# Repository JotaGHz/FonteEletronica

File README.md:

# Projeto Fonte de Tensão 12V, Eletrônica para Computação, BCC 020. ICMC USP São Carlos
## Grupo:
  ## Joao Francisco Caprioli Barbosa Camargo de Pinho
  ## 10748500
## O Projeto
Nesse projeto, o grupo deve desenvolver uma fonte de Tensão Variável de 3V a 12V, com capacidade de 100mA. Também, deve anexar ao projeto no GitHub o circuito no site de simulação Falstad, uma imagem do circuito no site, e uma simulação do projeto no EAGLE, junto com a simulação da placa do circuito.

  # Simulacão do Falstad
  
  http://tinyurl.com/ydexx9xs
  
  ## Imagem da Simulação
  
  # Componentes usados e preços
    
    Capacitor 470 uF  25V            R$  0,33
    Transformador 110/220V -> 12+12V R$ 16,45
    Resistor 1k *3                   R$  0,24
    Resistor 120 Ohms                R$  0,23
    Resistor 5k1                     R$  0,08
    Potenciômetro 10k   MAX=0,2W     R$  1,46
    LED Vermelho                     R$  0,24
    Diodo Zener 13V     MAX=0,5W     R$  0,14
    Ponte Retificadora   25A         R$  4,94
    Transistor NPN BC337             R$  0,17
    -----------------------------------------
    Total                            R$ 24,28
  # Explicação das peças escolhidas

## Transformador 127V para 24V
  O transformador é necessário para diminuir a voltagem que passa pelo circuito. Um transformador 5:1, ou transforma 127V em cerca de 24V, facilitou a escolha das outras peças, e deu uma margem de erro grande para o resto do circuito.

## Ponte Retificadora
  A ponte retificadora serve pra "converter" a corrente alternada em corrente contínua, gerando um polo positivo em cima e um negativo em baixo, olhando para o circuito no Falstad.

## Capacitor 470uF
  O capacitor "estabiliza" a tensão de 24V. O capacitor serve para manter a corrente estável quando ela alternar. Esse capacitor tem tensão máxima suportada de 35V, sendo perfeito para o circuito. Sem o capacitor, a tensão varia muito, e poderia queimar aparelhos conectados à fonte.

## LED Vermelho e Resistor 2k
  O LED Vermelho se conecta em paralelo com o capacitor. Sem nenhum resistor, o LED "quebraria" o circuito e causaria um curto-circuito, conectando os polos positivo e negativo. O uso de 2k Ohms é para diminuir a corrente gasta pelo LED, e ser um resistor fácil de construir em série com 2 resistores 1k.
  
## Diodo Zener
  O Diodo Zener serve para "separar" a voltagem do circuito. Sendo um Diodo Zener de 13V, ele só deixa aproximadamente 13V irem para o potenciômetro e para o resistor 5.1k do circuito.
  
## Potenciometro e Resistor 5.1k
  O Potenciômetro serve para o usuário regular a tensão entre 3V e 12V. O potenciômetro de 10k foi escolhido por ser facilmente encontrado e relativamente barato. Por conta do valor do potênciometro, o resistor 5.1k "estabiliza" a voltagem, tal qual o capacitor. Foi escolhido esse resistor por conta do preço.
  
## Transistor NPN
  O transistor permite a passagem da corrente para a saída, quando a tensão nele chega a 13V, tirando apenas 0.7V, transformando os 13V dados pelo Diodo Zener em 12.3V, com pequenas oscilações.
  # Arquivos do circuito e de impressão

  Esquemático simples do EAGLE, usado para fazer a placa de circuito na imagem seguinte:

  Imagem do PCB do circuito, usado para construir o circuito pessoalmente.
  
  # Apresentação
  ## Nota: O resistor de 100 Ohms acima do LED foi substituido por dois resistores de 1k em série, que no Falstad estão representados por um resistor 2k.
  Vídeo:
  https://www.youtube.com/watch?v=LuaJpIQDwXM
  
  # Turma BCC 020
  # Disciplina: SSC0180-Eletrônica para Computação

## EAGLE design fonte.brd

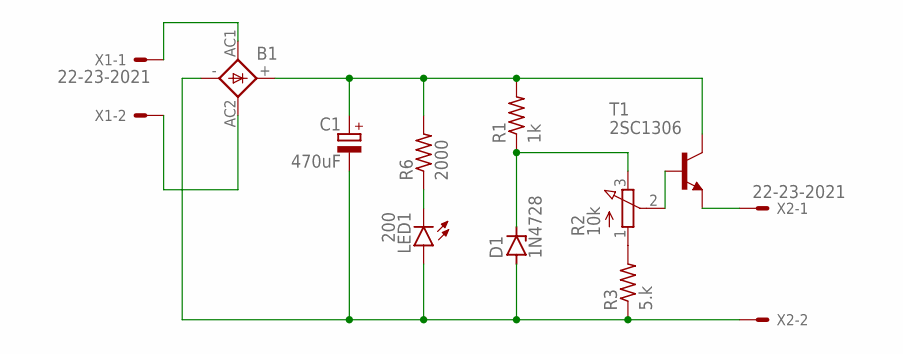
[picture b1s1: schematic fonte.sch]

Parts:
B1: GBPC1
C1: 470uF; B45181B
D1: 1N4728; DO41Z10
LED1: 200; LED3MM
R1: 1k; 0204/7
R2: 10k; 3RP/1610N
R3: 5.k; 0204/7
R6: 2000; 0204/7
T1: 2SC1306; TO220BV
X1, X2: 22-23-2021

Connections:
unnamed: B1.AC1, X1.1
unnamed: B1.AC2, X1.2
unnamed: B1.-, C1.-, D1.A, LED1.A, R3.1, X2.2
unnamed: B1.+, C1.+, R1.2, R6.2, T1.2 (C)
unnamed: D1.C, R1.1, R2.3 (E)
unnamed: R2.1 (A), R3.2
unnamed: R2.2 (S), T1.1 (B)
unnamed: T1.3 (E), X2.1
unnamed: LED1.K (C), R6.1

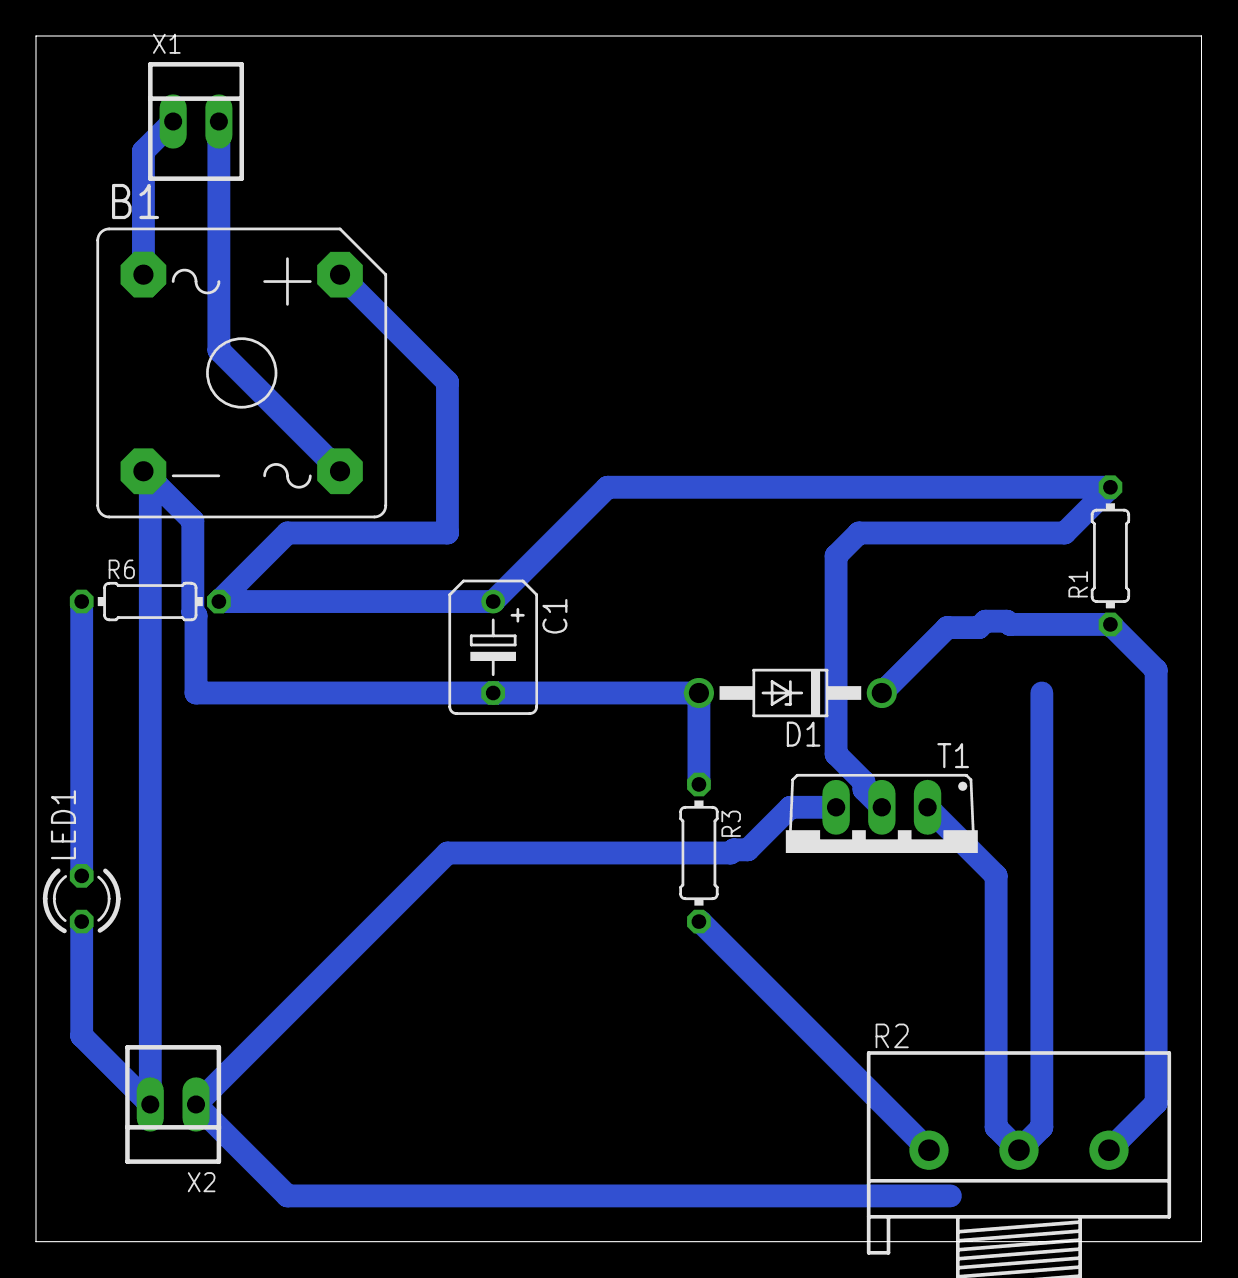
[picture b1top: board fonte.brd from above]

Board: 2 copper layers, 64.8 x 67.0 mm, 11 parts (0 on the bottom side), 9 nets.

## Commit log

2020-06-16 Add files via upload
    Circuito no Falstad
